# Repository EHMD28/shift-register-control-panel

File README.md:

# Shift Register Control Panel

The schematic is [available here](./assets/shift-register-control-panel.pdf). To order a PCB, download this project, and create a zip archive of the `gerbers` directory. Upload this archive to the PCB service when prompted.

Dimensions: 2.7228 x 1.6437 inches (4.475 in^2)

## To-Do

- [x] Change 330 Ω resistors to 1 kΩ in schematic to stay within current limits of 74HC595
- [ ] Add dimensions and other specs to the readme file.

## Bill of Materials

All packages are through-hole. 

| Name                   | Quantity | Value         | Purpose                               |
| ---------------------- | -------- | ------------- | ------------------------------------- |
| Capacitor              | 1        | 0.1 uF        | Input voltage smoothing               |
| 5 mm LED               | 9        | Red           | Output display (8), input display (1) |
| Resistor               | 9        | 1 kΩ          | LEDs                                  |
| Resistor               | 3        | 10 kΩ         | Pull-up/pull-down                     |
| Header Pins            | 1        | 1x08, 2.54 mm | Carry signal out                      |
| Push Button            | 3        | N/A           | Functions (display, clear, shift)     |
| Slide Switch           | 1        | N/A           | Input                                 |
| LM7805 (T0220 Package) | 1        | N/A           | Voltage regulator                     |
| 74HC595                | 1        | N/A           | 8-bit SIPO Shift Register Chip        |

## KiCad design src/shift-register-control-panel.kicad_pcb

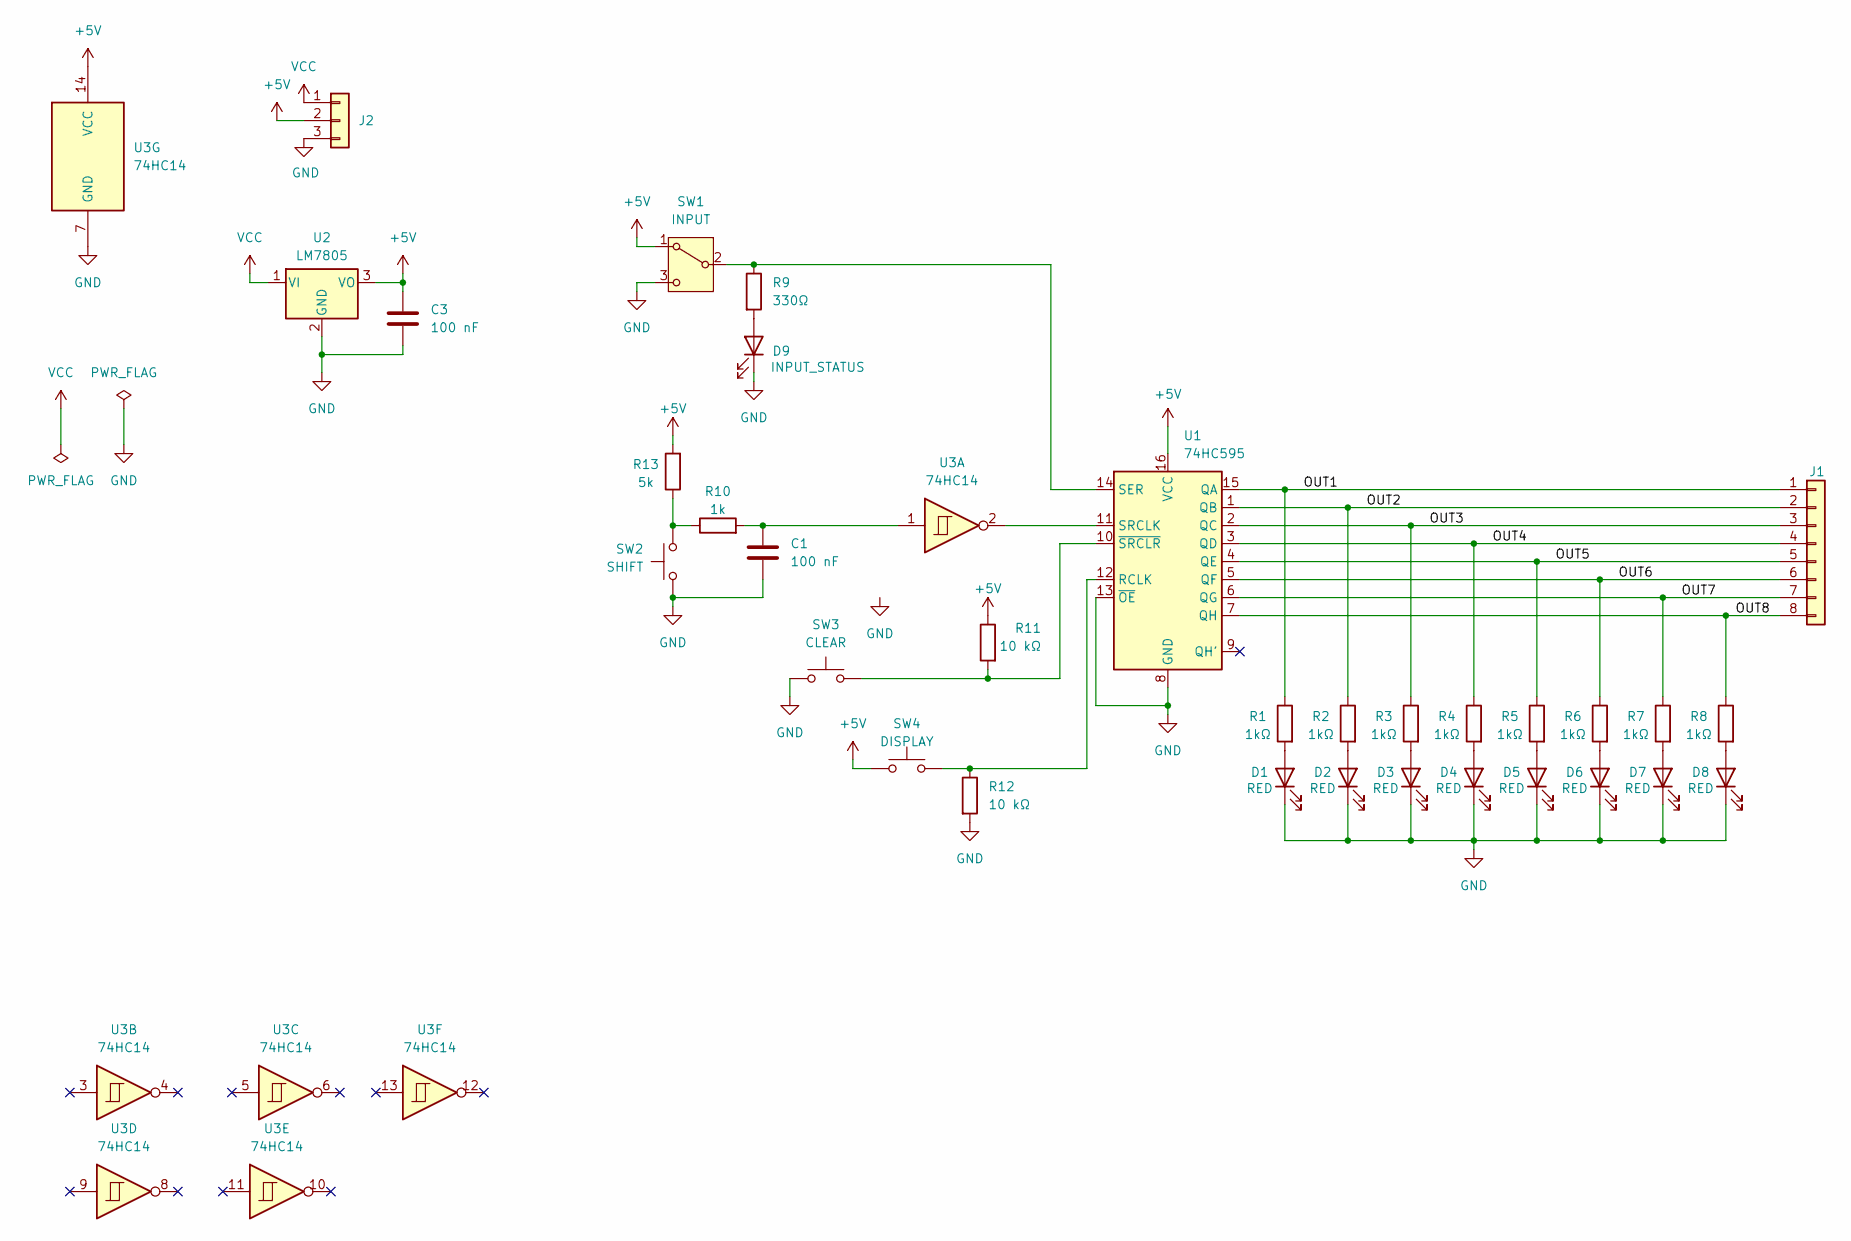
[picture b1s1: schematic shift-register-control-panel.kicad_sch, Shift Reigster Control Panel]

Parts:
C1: 100 nF; C_Disc_D5.0mm_W2.5mm_P5.00mm
C3: 100 nF
D1, D2, D3, D4, D5, D6, D7, D8: RED; LED_D5.0mm
D9: INPUT_STATUS; LED_D5.0mm
J1: Conn_01x08; PinHeader_1x08_P2.54mm_Vertical
J2: Conn_01x03
R1, R2, R3, R4, R5, R6, R7, R8: 1kΩ; R_Axial_DIN0204_L3.6mm_D1.6mm_P5.08mm_Horizontal
R9: 330Ω; R_Axial_DIN0204_L3.6mm_D1.6mm_P5.08mm_Horizontal
R10: 1k; R_Axial_DIN0204_L3.6mm_D1.6mm_P5.08mm_Horizontal
R11, R12: 10 kΩ; R_Axial_DIN0204_L3.6mm_D1.6mm_P5.08mm_Horizontal
R13: 5k; R_Axial_DIN0204_L3.6mm_D1.6mm_P5.08mm_Horizontal
SW1: INPUT; SW_Slide_SPDT_Straight_CK_OS102011MS2Q
SW2: SHIFT; SW_PUSH_6mm
SW3: CLEAR; SW_PUSH_6mm
SW4: DISPLAY; SW_PUSH_6mm
U1: 74HC595; DIP-16_W7.62mm_Socket
U2: LM7805; TO-220-3_Vertical
U3: 74HC14

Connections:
+5V: C3.1, J2.2, R11.1, R13.2, SW1.1 (A), SW4.1, U1.16 (VCC), U2.3 (VO), U3.14 (VCC)
/OUT1: J1.1, R1.1, U1.15 (QA)
/OUT2: J1.2, R2.1, U1.1 (QB)
/OUT3: J1.3, R3.1, U1.2 (QC)
/OUT4: J1.4, R4.1, U1.3 (QD)
/OUT5: J1.5, R5.1, U1.4 (QE)
/OUT6: J1.6, R6.1, U1.5 (QF)
/OUT7: J1.7, R7.1, U1.6 (QG)
/OUT8: J1.8, R8.1, U1.7 (QH)
GND: C1.2, C3.2, D1.1 (K), D2.1 (K), D3.1 (K), D4.1 (K), D5.1 (K), D6.1 (K), D7.1 (K), D8.1 (K), D9.1 (K), J2.3, R12.2, SW1.3 (C), SW2.1, SW3.1, U1.8 (GND), U1.13 (~OE), U2.2 (GND), U3.7 (GND)
unnamed: C1.1, R10.2, U3.1
unnamed: D1.2 (A), R1.2
unnamed: D2.2 (A), R2.2
unnamed: D3.2 (A), R3.2
unnamed: D4.2 (A), R4.2
unnamed: D5.2 (A), R5.2
unnamed: D6.2 (A), R6.2
unnamed: D7.2 (A), R7.2
unnamed: D8.2 (A), R8.2
unnamed: D9.2 (A), R9.2
unnamed: R10.1, R13.1, SW2.2
unnamed: R9.1, SW1.2 (B), U1.14 (SER)
unnamed: R12.1, SW4.2, U1.12 (RCLK)
unnamed: U1.11 (SRCLK), U3.2
unnamed: R11.2, SW3.2, U1.10 (~SRCLR)
VCC: J2.1, U2.1 (VI)

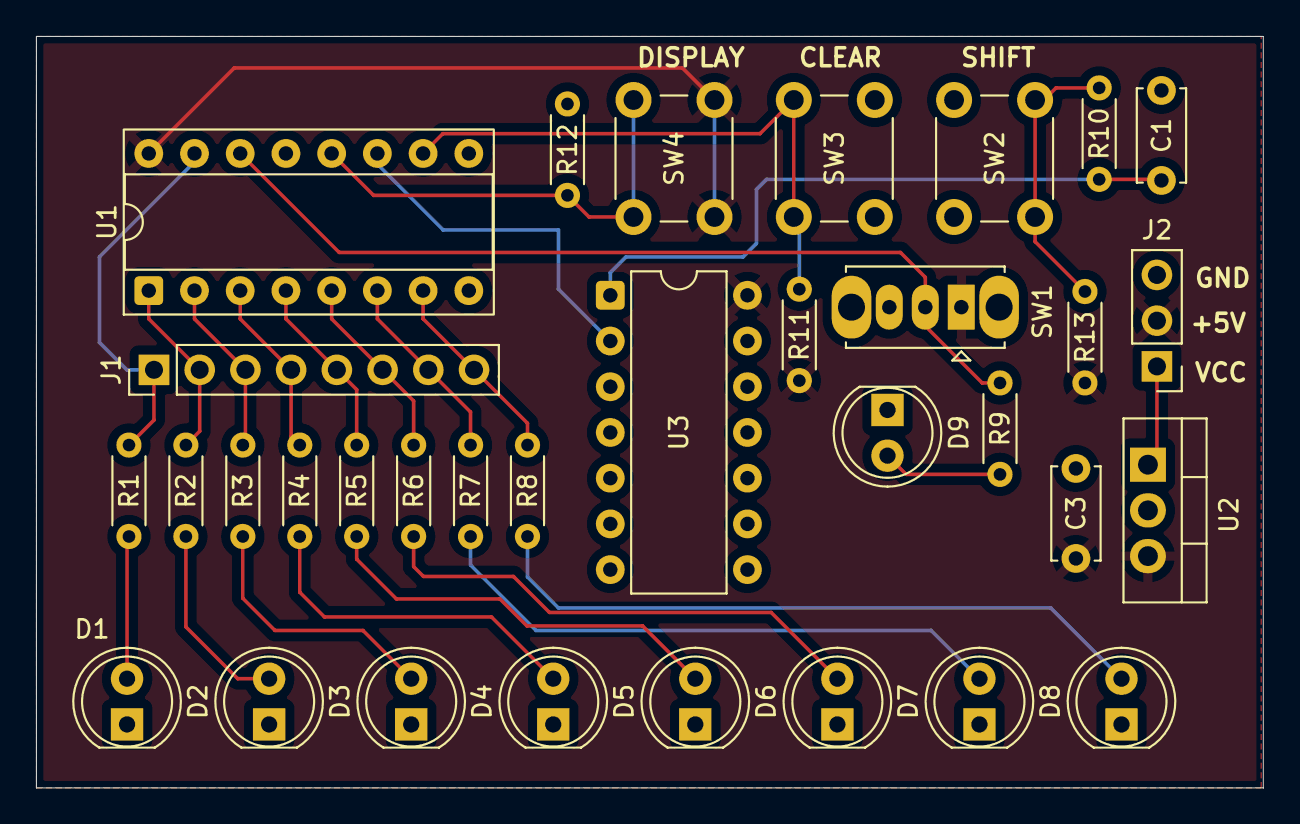
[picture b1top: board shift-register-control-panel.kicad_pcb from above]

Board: 2 copper layers, 68.2 x 41.8 mm, 33 parts (0 on the bottom side), 26 nets.
